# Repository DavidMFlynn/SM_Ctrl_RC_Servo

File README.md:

# SM_Ctrl_RC_Servo
Model railroad switch machine controller.
Uses a small (SG90) R/C Servo as a switch machine.
Built for the Highland Pacific, 854 East Broadway, San Gabriel, CA 91776, USA
GPL 3+
If you find it useful let me know dflynn at oxfordvue.com
The G2R Rev B may be the final version. A remote config connector and a big capacitor were added.
My faverite servo is the hobbyking HX5010 it's inexpensive and well behaved.

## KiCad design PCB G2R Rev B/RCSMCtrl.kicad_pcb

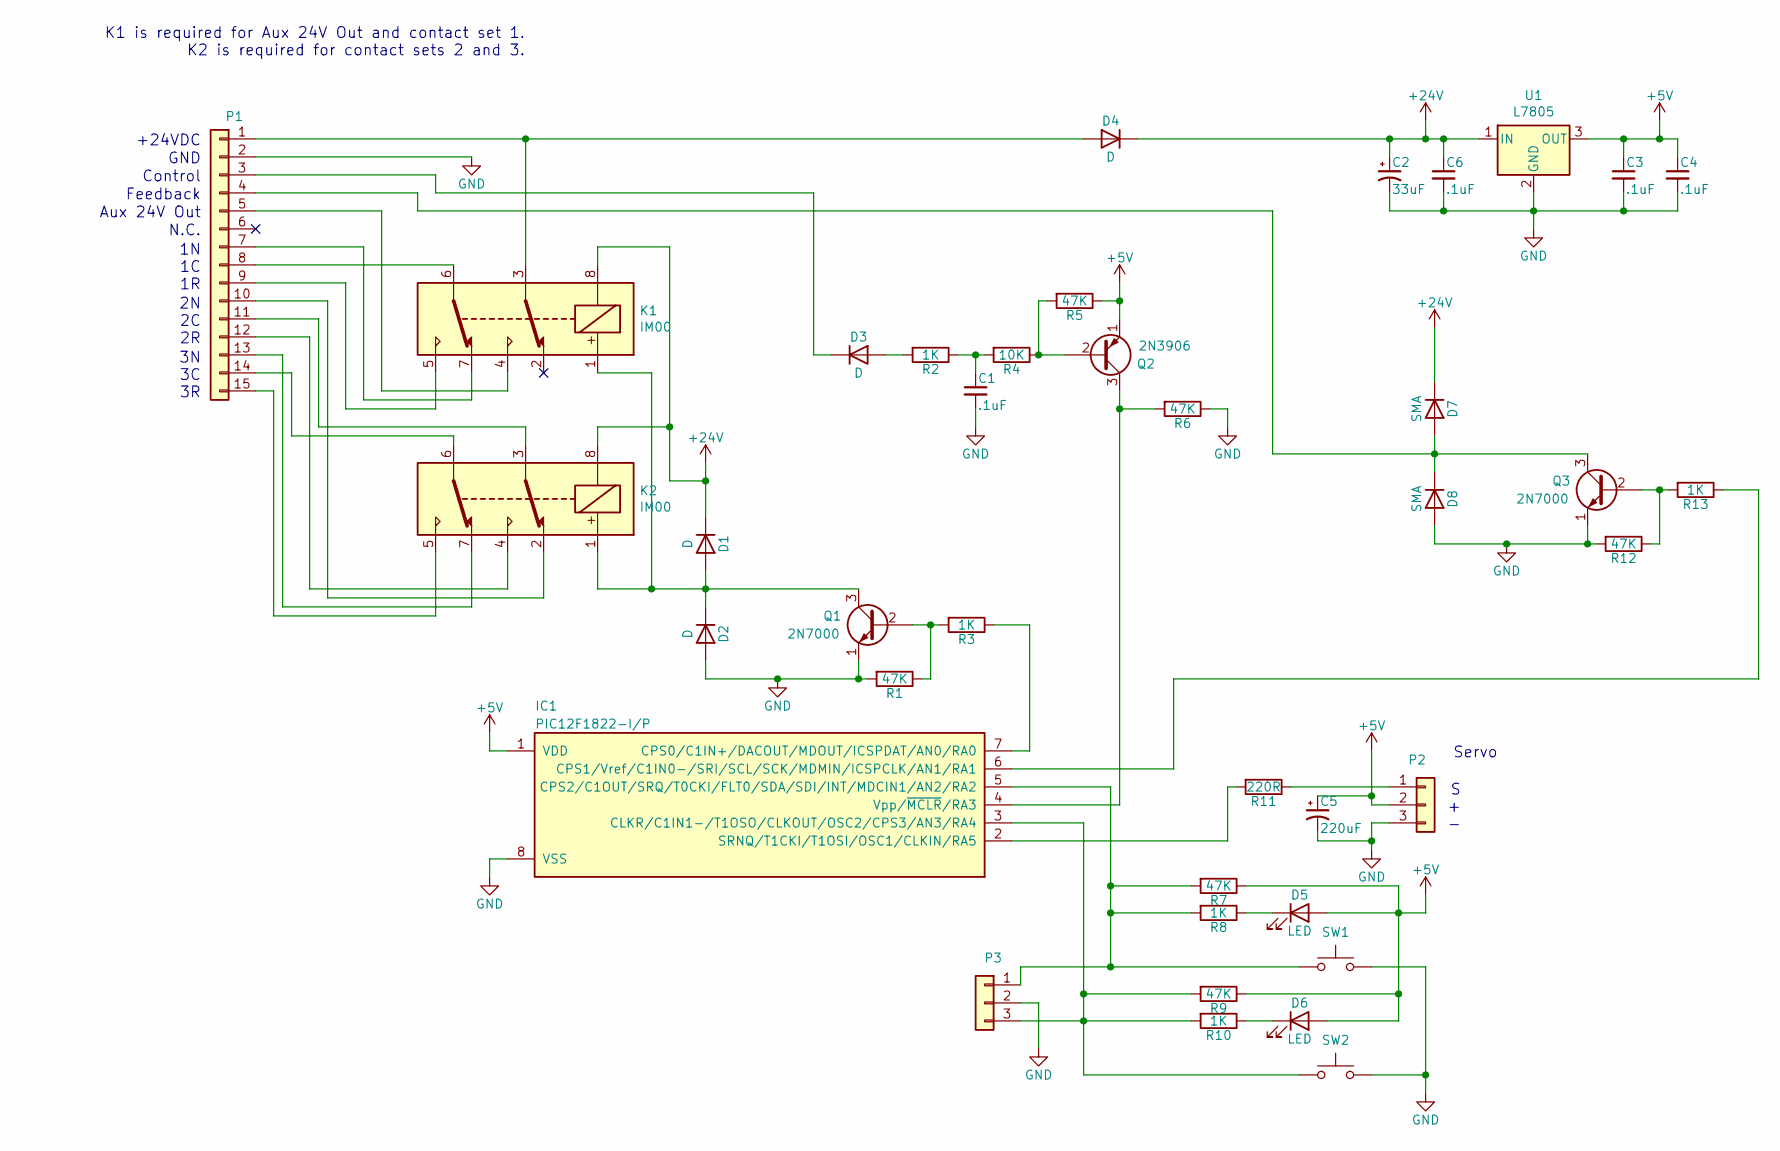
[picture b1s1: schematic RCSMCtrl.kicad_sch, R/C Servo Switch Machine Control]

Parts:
C1, C3, C4, C6: .1uF; C_0805_HandSoldering
C2: 33uF; Elko_vert_11.2x6.3mm_RM2.5_CopperClear
C5: 220uF; CP_Radial_D6.3mm_P2.50mm
D1, D2, D3, D4: D; Diode-SMA_Handsoldering
D5, D6: LED; LED-1206
D7, D8: SMA; Diode-SMA_Handsoldering
IC1: PIC12F1822-I/P; DIP-8_W7.62mm
K1, K2: IM00
P1: Conn_01x15
P2, P3: Conn_01x03; PinHeader_1x03_P2.54mm_Vertical
Q1, Q3: 2N7000; TO-92_Inline_Narrow_Oval
Q2: 2N3906; TO-92_Inline_Narrow_Oval
R1, R5, R6, R7, R9, R12: 47K; R_0805_HandSoldering
R2, R3, R8, R10, R13: 1K; R_0805_HandSoldering
R4: 10K; R_0805_HandSoldering
R11: 220R; R_0805_HandSoldering
SW1, SW2: SW_Push
U1: L7805

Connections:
+5V: C3.1, C4.1, C5.1, D5.2 (A), D6.2 (A), IC1.1 (VDD), P2.2, Q2.1 (E), R5.1, R7.1, R9.1, U1.3 (OUT)
+24V: C2.1, C6.1, D1.1 (K), D4.1 (K), D7.1 (K), K1.8, K2.8, U1.1 (IN)
GND: C1.2, C2.2, C3.2, C4.2, C5.2, C6.2, D2.2 (A), D8.2 (A), IC1.8 (VSS), P1.2, P2.3, P3.2, Q1.1 (E), Q3.1 (E), R1.2, R6.1, R12.2, SW1.2, SW2.2, U1.2 (GND)
unnamed: C1.1, R2.1, R4.2
unnamed: D1.2 (A), D2.1 (K), K1.1, K2.1, Q1.3 (C)
unnamed: D3.1 (K), P1.3
unnamed: D3.2 (A), R2.2
unnamed: D4.2 (A), K1.3, P1.1
unnamed: D5.1 (K), R8.1
unnamed: D6.1 (K), R10.1
unnamed: D7.2 (A), D8.1 (K), P1.4, Q3.3 (C)
unnamed: IC1.2 (SRNQ/T1CKI/T1OSI/OSC1/CLKIN/RA5), R11.2
unnamed: IC1.3 (CLKR/C1IN1-/T1OSO/CLKOUT/OSC2/CPS3/AN3/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), P3.3, R9.2, R10.2, SW2.1
unnamed: IC1.4 (Vpp/~MCLR~/RA3), Q2.3 (C), R6.2
unnamed: IC1.5 (CPS2/C1OUT/SRQ/T0CKI/FLT0/SDA/SDI/INT/M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), P3.1, R7.2, R8.2, SW1.1
unnamed: IC1.6 (CPS1/Vref/C1IN0-/SRI/SCL/SCK/MDMIN/ICSP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), R13.1
unnamed: IC1.7 (CPS0/C1IN+/DACOUT/MDOUT/ICSPDAT/AN0/RA0), R3.1
unnamed: K1.4, P1.5
unnamed: K1.5, P1.9
unnamed: K1.6, P1.8
unnamed: K1.7, P1.7
unnamed: K2.2, P1.10
unnamed: K2.3, P1.11
unnamed: K2.4, P1.12
unnamed: K2.5, P1.15
unnamed: K2.6, P1.14
unnamed: K2.7, P1.13
unnamed: P2.1, R11.1
unnamed: Q1.2 (B), R1.1, R3.2
unnamed: Q2.2 (B), R4.1, R5.2
unnamed: Q3.2 (B), R12.1, R13.2

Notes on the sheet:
+24VDC
GND
Control
Feedback
Aux 24V Out
N.C.
1N 1C 1R
2N 2C 2R
3N 3C 3R
K1 is required for Aux 24V Out and contact set 1. K2 is required for contact sets 2 and 3.
Servo
S + -

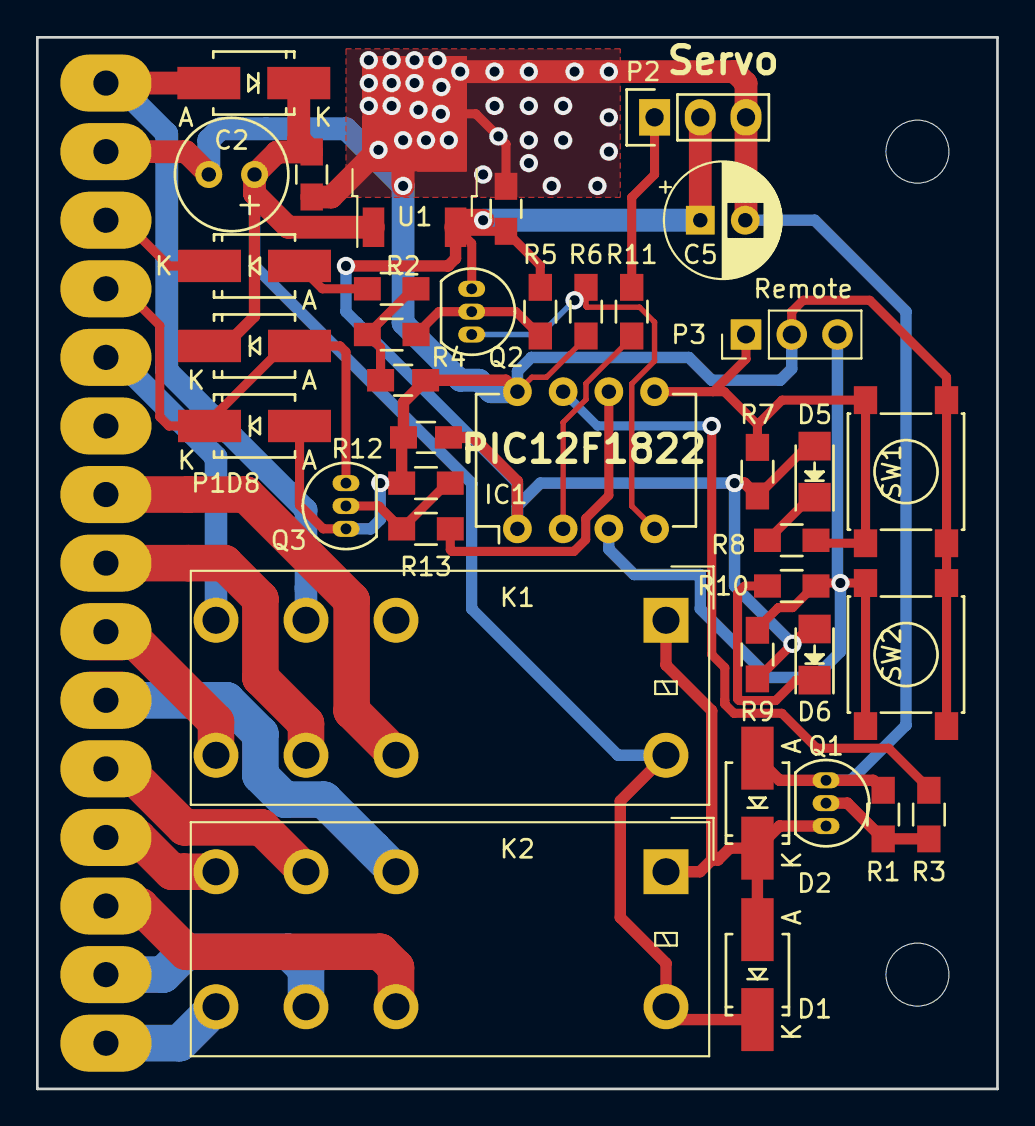
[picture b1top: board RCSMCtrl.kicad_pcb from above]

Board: 2 copper layers, 53.3 x 58.4 mm, 41 parts (0 on the bottom side), 31 nets.

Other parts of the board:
H1, H2: MountingHole_3-5mm

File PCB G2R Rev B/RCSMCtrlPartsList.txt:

R/C Servo Sitch Machine Controller Parts List
=========================================================
P1	Wires 15 x 10" 20AWG
P2	Connector 3 pin .1cl

K1,K2	Relay G2R 24VDC DPDT (1 or 2)

U1	LM7805 DPAK
IC1	Socket 8 pin dip (optional)
IC1	PIC12F1822

Q1,Q3	2N7000 40V N-Ch FET TO-92 (2)
Q2	2N3906 40V PNP TO-92

D1,D2,D3,D4,D7,D8	Diode 200V Fast SMA (6)
D5,D6	LED 1206 (2)
SW1,SW1	Switch SMT SPST

C1,C3,C4,C6	Cap 0.1uf 0805 (3)
C2	Cap 33uf 50v
C5                     Cap 220uf 16v

R1,R5,R6,R7,R9,R12	Res 47KΩ 0805 (6)
R2,R3,R8,R10,R13	Res 1KΩ 0805 (5)
R4	Res 10KΩ 0805
R11	Res 220Ω 0805

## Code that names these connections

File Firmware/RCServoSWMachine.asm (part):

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;====================================================================================================
;
;  Pin 1 VDD (+5V)		+5V
;  Pin 2 RA5		CCP1
;  Pin 3 RA4		System LED Active Low/SW2 Dec switch Active Low
;  Pin 4 RA3/MCLR*/Vpp (Input only)	Command = Active High
;  Pin 5 RA2		LED 2 Active Low/SW1 Inc switch Active Low
;  Pin 6 RA1/ICSPCLK		Feedback Active High Output
;  Pin 7 RA0/ICSPDAT		Relay Control Active High Output
;  Pin 8 VSS (Ground)		Ground
;
;====================================================================================================
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
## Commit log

2015-11-11 PCB is here, Firmware is next
2017-09-20 Here it is
2019-07-14 2C Mini Version
2019-07-15 Update 7/15
2019-07-16 servo mount
2019-07-19 thinking about slow mover
2019-07-21 Slower
2019-07-21 Switching regulator
2019-08-06 Startup at correct position
2019-08-07 1.0b4 FC1
2019-08-09 A better block
2019-08-24 mini rev A
2019-10-25 G2R Rev B
2019-10-25 nothing
2019-11-27 ready to print
2020-10-21 Atlas turnout driver (proto)
2020-10-21 Adjusted width
2020-10-22 added lock and mirror versions
2020-11-15 Mounting...
2020-11-17 extensions
2020-11-18 extender
2020-11-19 worked on RA mount
2020-11-19 RA work...
2020-11-21 V1.2.2 FC1
2020-11-21 RA mount #4 bolt
2020-12-17 Fixed for MacroPIC
